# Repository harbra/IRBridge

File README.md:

# IRBridge - controlling IR devices via Alexa and webinterface

## Project description
The IRBridge can record and emit infrared commands - configured by a webinterface, accessible via Alexa, running on an ESP8266.

A more detailed description can be found on [hackster.io](https://www.hackster.io/har-bra/irbridge-controlling-ir-devices-via-alexa-and-webinterface-66ca06).

## Repository contents
* C++ code that is running on the ESP8266, based on the Arduino core (in /code/esp8266)
* HTML/CSS/JS for webinterface, based on vue.js and Bulma (in /code/web)
* Schematic and PCB for the underlying electronics, created in KiCAD (in /pcb)
* Enclosure design, created in FreeCAD (in /cad)

## Licenses
* All code is licensed with the [MIT license](https://opensource.org/licenses/MIT)
* Schematic, PCB and enclosure design are licensed with [CC-BY-SA-4.0](https://creativecommons.org/licenses/by-sa/4.0/)

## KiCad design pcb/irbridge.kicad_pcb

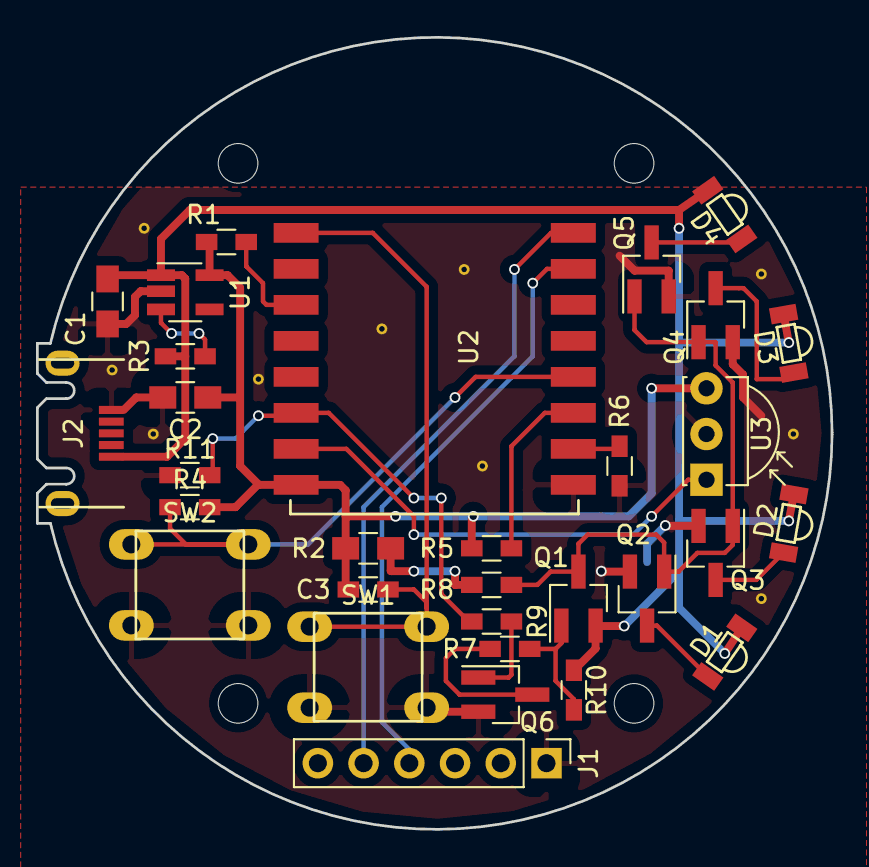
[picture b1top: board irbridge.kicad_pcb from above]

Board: 2 copper layers, 44.1 x 44.0 mm, 45 parts (0 on the bottom side), 21 nets.

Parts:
C1, C2, C3: 10µ; C_0805_HandSoldering
D1, D2, D3, D4: VSMB2948SL
H1, H2, H3, H4: MountingHole_2.2mm_M2
J1: CONN_01X06; Pin_Header_Straight_1x06_Pitch2.54mm
J2: 1051640001
Q1: PN2907; SOT-23_Handsoldering
Q2, Q3, Q4, Q5, Q6: 2N3904; SOT-23_Handsoldering
R1, R2, R3, R4, R5, R6, R8, R10: 10k; R_0603_HandSoldering
R7, R9, R11: 1k; R_0603_HandSoldering
SW1, SW2: SW_Push; 450-1804-ND
U1: AP2112; SOT-23-5_HandSoldering
U2: ESP-12; ESP-12S_SMD
U3: TSOP43xx; IRReceiver_Vishay_MOLD-3pin
r: v; Via-0.6mm
r#2, r#3, r#4, r#5, r#6, r#7, r#8, r#9, r#10: v; Via-0.6mm

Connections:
+3V3: C2.2, C3.2, R1.1, R2.1, R4.1, R5.1, U1.5, U2.8, U3.3
+5V: C1.2, D1.2, D2.2, D3.2, D4.2, J2.1, Q1.2, R3.2, R10.2, U1.1
/ESP_RX: J1.4, U2.15
/ESP_TX: J1.5, U2.16
GND: C1.1, C2.1, C3.1, J1.1, J2.5, Q2.2, Q3.2, Q4.2, Q5.2, Q6.2, R6.1, R8.2, R11.1, SW1.1, SW2.1, U1.2, U2.9, U3.2, r.1, r#2.1, r#3.1, r#4.1, r#5.1, r#6.1, r#7.1, r#8.1, r#9.1, r#10.1
unnamed: D1.1, Q2.3
unnamed: D2.1, Q3.3
unnamed: D3.1, Q4.3
unnamed: D4.1, Q5.3
unnamed: Q1.1, R7.1, R10.1
unnamed: Q1.3, Q2.1, Q3.1, Q4.1, Q5.1, R8.1
unnamed: Q6.1, R9.1
unnamed: Q6.3, R7.2
unnamed: R1.2, U2.3
unnamed: R2.2, SW1.2, U2.1
unnamed: R3.1, U1.3
unnamed: R4.2, SW2.2, U2.12
unnamed: R5.2, U2.11
unnamed: R6.2, U2.10
unnamed: R9.2, R11.2, U2.6
unnamed: U2.7, U3.1

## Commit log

2018-03-04 added test comment
2018-03-13 Migrated IRBridge to new directory structure. Prepared content for GitHub upload.
2018-03-13 Last minute fixes.
2018-03-31 Added KiCad library for custom components.
2018-04-07 Corrected error in silkscreentext. R2 and C3 were mixed up.
2018-06-26 Fixed non-working /api/sendir handler.
2019-01-04 Reflected new functionality of choosing lwip via platformio.ini.
